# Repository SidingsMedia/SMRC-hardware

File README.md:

<!-- 
SPDX-FileCopyrightText: Copyright (c) 2021 Matthew Nickson 

SPDX-License-Identifier: MIT
-->
# Hardware

This repository contains all of the schematics and PCB files for Sidings
Media Railway Controller. 

## Main Control Board

This is the main component of the SMRC system. It provides a bridge
between the control nodes and the user as well as handling all of the
railway control logic.

## Speed Control Board

This is one of the nodes that helps to control the railway. It provides
power and controls the speed of a train on the tracks

## Relay Board

This node controls isolation sections in your track allowing for
multiple trains to be on the same line without having to use DCC. It has
8 channels allowing for up to 8 seperate isolation sections to be
controlled from one speed controller.

# Licence
This repo uses the [REUSE](https://reuse.software) standard in order to communicate the correct licence for the file. For those unfamiliar with the standard the licence for each file can be found in one of three places. The licence will either be in a comment block at the top of the file, in a `.license` file with the same name as the file, or in the dep5 file located in the `.reuse` directory. If you are unsure of the licencing terms please contact [contact@sidingsmedia.com](mailto:contact@sidingsmedia.com?subject=SMRC%20Licence). All files committed to this repo must contain valid licencing information or the pull request can not be accepted.

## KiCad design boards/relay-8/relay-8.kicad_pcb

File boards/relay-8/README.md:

# 8 Channel relay

This board controls the flow of electricity to the rails when the
railway is in operation allowing for isolation sections to be created.

## Bill of materials

Total number of components: 75

|Ref                                          |Qnty|Value               |Cmp name            |Footprint                                             |Description                                                                                                |Vendor|
|---------------------------------------------|----|--------------------|--------------------|------------------------------------------------------|-----------------------------------------------------------------------------------------------------------|------|
|C1, C3, C5,                                  |3   |1uF                 |C                   |Capacitor_SMD:CP_Elec_4x3                             |Unpolarized capacitor                                                                                      |      |
|C2,                                          |1   |0.1uF               |CP                  |Capacitor_SMD:CP_Elec_4x3                             |                                                                                                           |      |
|C4,                                          |1   |100nF               |C                   |Capacitor_SMD:C_0805_2012Metric                       |Unpolarized capacitor                                                                                      |      |
|D1, D2, D5, D6, D9, D10, D13, D14, D17, D18, |10  |LED                 |LED                 |LED_SMD:LED_0805_2012Metric                           |Light emitting diode                                                                                       |      |
|D3, D4, D7, D8, D11, D12, D15, D16,          |8   |1N5819              |1N5819              |Diode_SMD:D_SMA                                       |40V 1A Schottky Barrier Rectifier Diode, DO-41                                                             |      |
|J1, J3, J4, J5, J6, J7, J8, J9, J10, J11,    |10  |Screw_Terminal_01x02|Screw_Terminal_01x02|TerminalBlock:TerminalBlock_bornier-2_P5.08mm         |Generic screw terminal, single row, 01x02, script generated (kicad-library-utils/schlib/autogen/connector/)|      |
|J2,                                          |1   |USB_B_Micro         |USB_B_Micro         |Connector_USB:USB_Micro-B_Molex_47346-0001            |USB Micro Type B connector                                                                                 |      |
|K1, K2, K3, K4, K5, K6, K7, K8,              |8   |RT42xxxx            |RT42xxxx            |Relay_THT:Relay_DPDT_Schrack-RT2-FormC_RM5mm          |Schrack RT2 relay, monostable dual pole dual throw, DC or AC coil                                          |      |
|Q1, Q2, Q3, Q4, Q5, Q6, Q7, Q8,              |8   |BC847               |BC847               |Package_TO_SOT_SMD:SOT-23                             |0.1A Ic, 45V Vce, NPN Transistor, SOT-23                                                                   |      |
|R1,                                          |1   |10K                 |R                   |Resistor_SMD:R_0805_2012Metric                        |Resistor                                                                                                   |      |
|R2,                                          |1   |560R                |R                   |Resistor_SMD:R_0805_2012Metric                        |Resistor                                                                                                   |      |
|R3, R4, R5, R8, R9, R12, R13, R16, R17,      |9   |330R                |R                   |Resistor_SMD:R_0805_2012Metric                        |Resistor                                                                                                   |      |
|R6, R7, R10, R11, R14, R15, R18, R19,        |8   |1K                  |R                   |Resistor_SMD:R_0805_2012Metric                        |Resistor                                                                                                   |      |
|R20, R21,                                    |2   |R                   |R                   |Resistor_SMD:R_0805_2012Metric                        |Resistor                                                                                                   |      |
|SW1,                                         |1   |SW_Push             |SW_Push             |Button_Switch_SMD:SW_Push_1P1T_NO_6x6mm_H9.5mm        |Push button switch, generic, two pins                                                                      |      |
|U1,                                          |1   |ESP32-WROOM-32D     |ESP32-WROOM-32D     |RF_Module:ESP32-WROOM-32                              |RF Module, ESP32-D0WD SoC, Wi-Fi 802.11b/g/n, Bluetooth, BLE, 32-bit, 2.7-3.6V, onboard antenna, SMD       |      |
|U2,                                          |1   |MCP2200-I-MQ        |MCP2200-I-MQ        |Package_DFN_QFN:QFN-20-1EP_5x5mm_P0.65mm_EP3.35x3.35mm|USB 2.0 to UART Protocol Converter with GPIO, QFN-20                                                       |      |
|U3,                                          |1   |LM317_SOT-223       |LM317_SOT-223       |Package_TO_SOT_SMD:SOT-223-3_TabPin2                  |1.5A 35V Adjustable Linear Regulator, SOT-223                                                              |      |

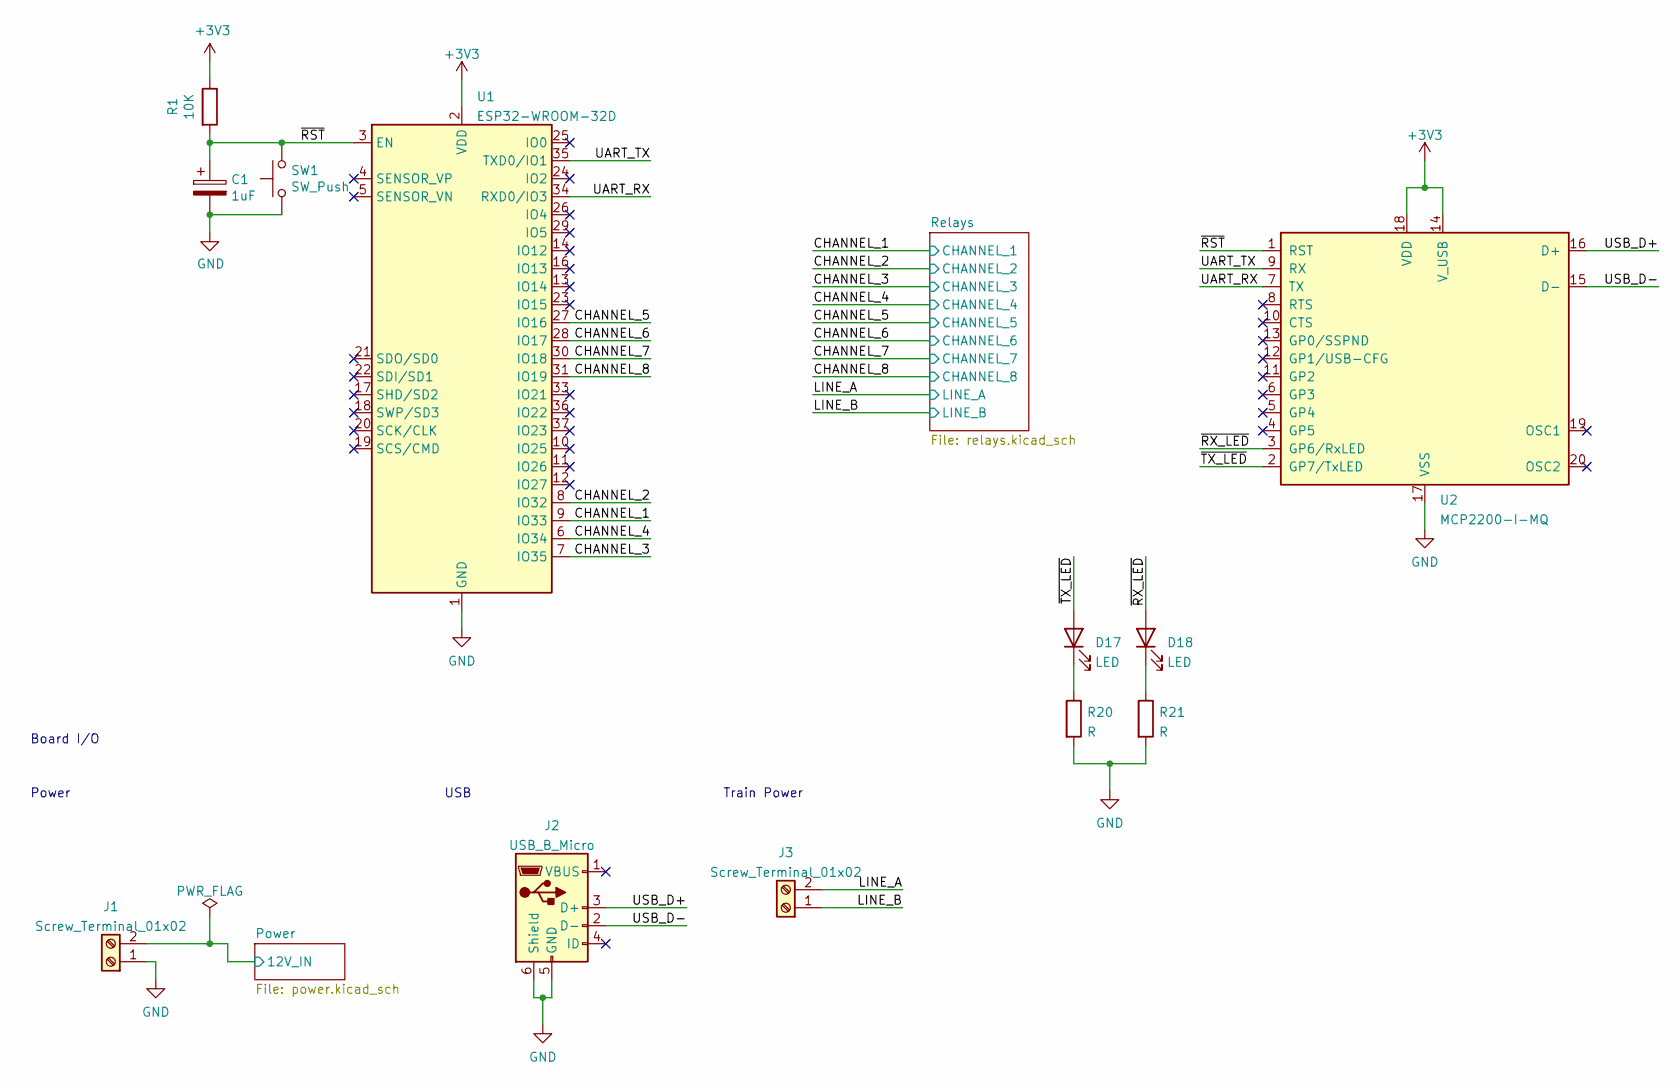
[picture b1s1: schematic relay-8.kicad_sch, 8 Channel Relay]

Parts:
C1: 1uF; CP_Elec_4x3
D17, D18: LED; LED_0805_2012Metric
J1, J3: Screw_Terminal_01x02; TerminalBlock_bornier-2_P5.08mm
J2: USB_B_Micro; USB_Micro-B_Molex_47346-0001
R1: 10K; R_0805_2012Metric
R20, R21: R; R_0805_2012Metric
SW1: SW_Push; SW_Push_1P1T_NO_6x6mm_H9.5mm
U1: ESP32-WROOM-32D; ESP32-WROOM-32
U2: MCP2200-I-MQ; QFN-20-1EP_5x5mm_P0.65mm_EP3.35x3.35mm

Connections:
+3V3: R1.1, U1.2 (VDD), U2.14 (V_USB), U2.18 (VDD); also elsewhere on the board
+12V: J1.2; also elsewhere on the board
/CHANNEL_1: U1.9 (IO33); also elsewhere on the board
/CHANNEL_2: U1.8 (IO32); also elsewhere on the board
/CHANNEL_3: U1.7 (IO35); also elsewhere on the board
/CHANNEL_4: U1.6 (IO34); also elsewhere on the board
/CHANNEL_5: U1.27 (IO16); also elsewhere on the board
/CHANNEL_6: U1.28 (IO17); also elsewhere on the board
/CHANNEL_7: U1.30 (IO18); also elsewhere on the board
/CHANNEL_8: U1.31 (IO19); also elsewhere on the board
/LINE_A: J3.2; also elsewhere on the board
/LINE_B: J3.1; also elsewhere on the board
/UART_RX: U1.34 (RXD0/IO3), U2.7 (TX)
/UART_TX: U1.35 (TXD0/IO1), U2.9 (RX)
/USB_D+: J2.3 (D+), U2.16 (D+)
/USB_D-: J2.2 (D-), U2.15 (D-)
/~RST: C1.1, R1.2, SW1.2, U1.3 (EN), U2.1 (RST)
/~RX_LED: D18.2 (A), U2.3 (GP6/RxLED)
/~TX_LED: D17.2 (A), U2.2 (GP7/TxLED)
GND: C1.2, J1.1, J2.5 (GND), J2.6 (Shield), R20.2, R21.2, SW1.1, U1.1 (GND), U1.15 (GND), U1.38 (GND), U1.39 (GND), U2.17 (VSS); also elsewhere on the board
unnamed: D17.1 (K), R20.1
unnamed: D18.1 (K), R21.1

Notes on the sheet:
Train Power
Board I/O
Power
USB

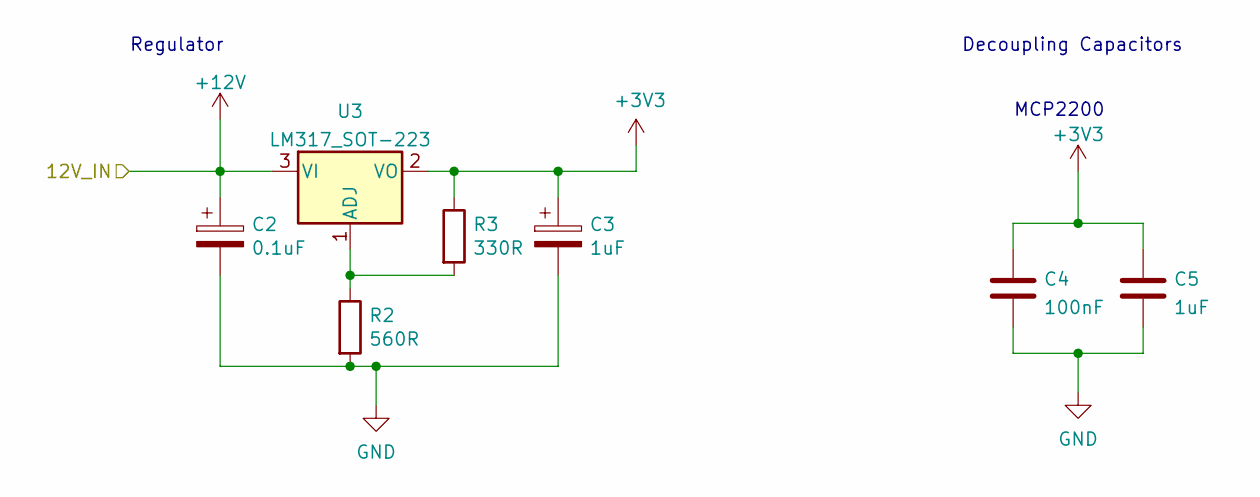
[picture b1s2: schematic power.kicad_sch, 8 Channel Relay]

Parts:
C2: 0.1uF; CP_Elec_4x3
C3, C5: 1uF; CP_Elec_4x3
C4: 100nF; C_0805_2012Metric
R2: 560R; R_0805_2012Metric
R3: 330R; R_0805_2012Metric
U3: LM317_SOT-223; SOT-223-3_TabPin2

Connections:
+3V3: C3.1, C4.1, C5.1, R3.1, U3.2 (VO); also elsewhere on the board
+12V: C2.1, U3.3 (VI); also elsewhere on the board
GND: C2.2, C3.2, C4.2, C5.2, R2.2; also elsewhere on the board
unnamed: R2.1, R3.2, U3.1 (ADJ)

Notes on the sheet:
Regulator
Decoupling Capacitors
MCP2200

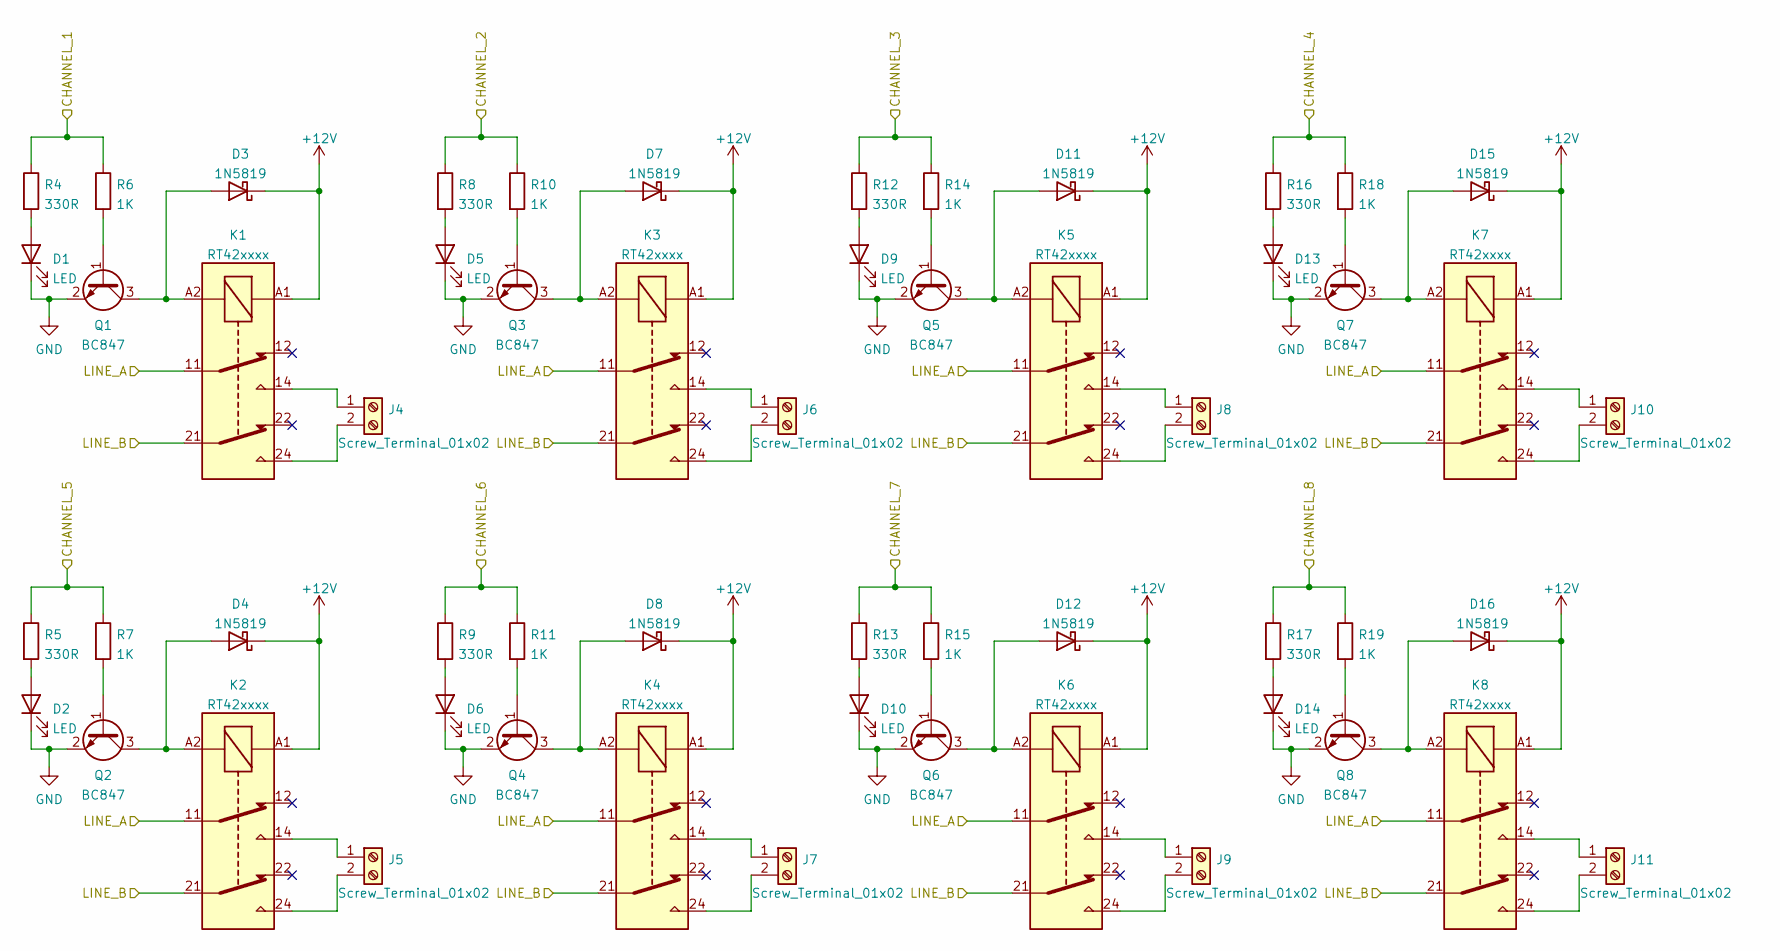
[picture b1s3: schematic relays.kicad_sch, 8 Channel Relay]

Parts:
D1, D2, D5, D6, D9, D10, D13, D14: LED; LED_0805_2012Metric
D3, D4, D7, D8, D11, D12, D15, D16: 1N5819; D_SMA
J4, J5, J6, J7, J8, J9, J10, J11: Screw_Terminal_01x02; TerminalBlock_bornier-2_P5.08mm
K1, K2, K3, K4, K5, K6, K7, K8: RT42xxxx; Relay_DPDT_Schrack-RT2-FormC_RM5mm
Q1, Q2, Q3, Q4, Q5, Q6, Q7, Q8: BC847; SOT-23
R4, R5, R8, R9, R12, R13, R16, R17: 330R; R_0805_2012Metric
R6, R7, R10, R11, R14, R15, R18, R19: 1K; R_0805_2012Metric

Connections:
+12V: D3.1 (K), D4.1 (K), D7.1 (K), D8.1 (K), D11.1 (K), D12.1 (K), D15.1 (K), D16.1 (K), K1.A1, K2.A1, K3.A1, K4.A1, K5.A1, K6.A1, K7.A1, K8.A1; also elsewhere on the board
/CHANNEL_1: R4.1, R6.1; also elsewhere on the board
/CHANNEL_2: R8.1, R10.1; also elsewhere on the board
/CHANNEL_3: R12.1, R14.1; also elsewhere on the board
/CHANNEL_4: R16.1, R18.1; also elsewhere on the board
/CHANNEL_5: R5.1, R7.1; also elsewhere on the board
/CHANNEL_6: R9.1, R11.1; also elsewhere on the board
/CHANNEL_7: R13.1, R15.1; also elsewhere on the board
/CHANNEL_8: R17.1, R19.1; also elsewhere on the board
/LINE_A: K1.11, K2.11, K3.11, K4.11, K5.11, K6.11, K7.11, K8.11; also elsewhere on the board
/LINE_B: K1.21, K2.21, K3.21, K4.21, K5.21, K6.21, K7.21, K8.21; also elsewhere on the board
GND: D1.1 (K), D2.1 (K), D5.1 (K), D6.1 (K), D9.1 (K), D10.1 (K), D13.1 (K), D14.1 (K), Q1.2 (E), Q2.2 (E), Q3.2 (E), Q4.2 (E), Q5.2 (E), Q6.2 (E), Q7.2 (E), Q8.2 (E); also elsewhere on the board
unnamed: D1.2 (A), R4.2
unnamed: D2.2 (A), R5.2
unnamed: D3.2 (A), K1.A2, Q1.3 (C)
unnamed: D4.2 (A), K2.A2, Q2.3 (C)
unnamed: D5.2 (A), R8.2
unnamed: D6.2 (A), R9.2
unnamed: D7.2 (A), K3.A2, Q3.3 (C)
unnamed: D8.2 (A), K4.A2, Q4.3 (C)
unnamed: D9.2 (A), R12.2
unnamed: D10.2 (A), R13.2
unnamed: D11.2 (A), K5.A2, Q5.3 (C)
unnamed: D12.2 (A), K6.A2, Q6.3 (C)
unnamed: D13.2 (A), R16.2
unnamed: D14.2 (A), R17.2
unnamed: D15.2 (A), K7.A2, Q7.3 (C)
unnamed: D16.2 (A), K8.A2, Q8.3 (C)
unnamed: J4.1, K1.14
unnamed: J4.2, K1.24
unnamed: J5.1, K2.14
unnamed: J5.2, K2.24
unnamed: J6.1, K3.14
unnamed: J6.2, K3.24
unnamed: J7.1, K4.14
unnamed: J7.2, K4.24
unnamed: J8.1, K5.14
unnamed: J8.2, K5.24
unnamed: J9.1, K6.14
unnamed: J9.2, K6.24
unnamed: J10.1, K7.14
unnamed: J10.2, K7.24
unnamed: J11.1, K8.14
unnamed: J11.2, K8.24
unnamed: Q1.1 (B), R6.2
unnamed: Q2.1 (B), R7.2
unnamed: Q3.1 (B), R10.2
unnamed: Q4.1 (B), R11.2
unnamed: Q5.1 (B), R14.2
unnamed: Q6.1 (B), R15.2
unnamed: Q7.1 (B), R18.2
unnamed: Q8.1 (B), R19.2

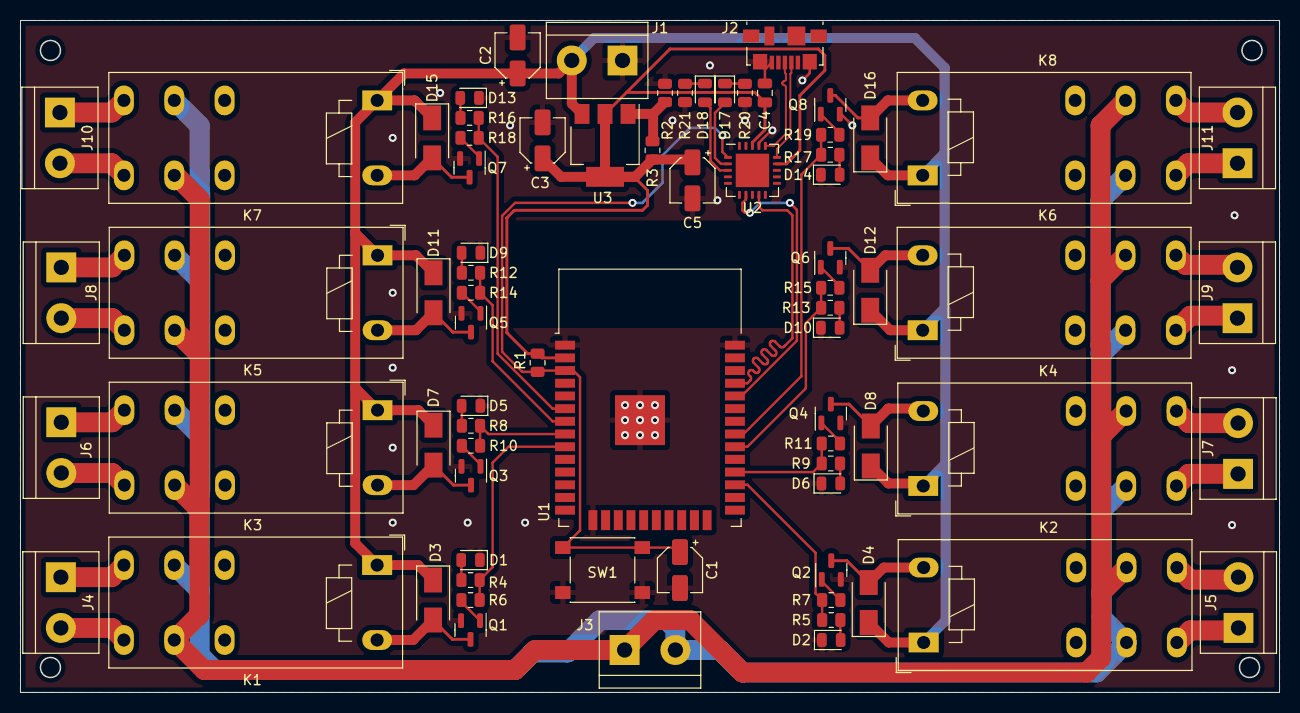
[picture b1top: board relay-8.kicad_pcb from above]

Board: 2 copper layers, 126.0 x 67.2 mm, 75 parts (0 on the bottom side), 63 nets.

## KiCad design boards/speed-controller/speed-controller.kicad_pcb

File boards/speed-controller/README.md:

# Speed controller

This board controls the speed of the trains running on the tracks.

## Bill of materials

Total number of components: 35

|Ref                  |Qnty|Value               |Cmp name            |Footprint                                                               |Description                                                                                                |Vendor|
|---------------------|----|--------------------|--------------------|------------------------------------------------------------------------|-----------------------------------------------------------------------------------------------------------|------|
|C1, C2,              |2   |0.1uF               |CP                  |Capacitor_SMD:CP_Elec_4x3                                               |                                                                                                           |      |
|C3, C4, C6,          |3   |1uF                 |C_Polarized         |Capacitor_SMD:CP_Elec_4x3                                               |Polarized capacitor                                                                                        |      |
|D1, D2, D3, D4,      |4   |1N5820              |1N5820              |Diode_SMD:D_SMC                                                         |20V 3A Schottky Barrier Rectifier Diode, DO-201AD                                                          |      |
|D5, D6,              |2   |LED                 |LED                 |LED_SMD:LED_0805_2012Metric                                             |Light emitting diode                                                                                       |      |
|J1, J2, J3,          |3   |Screw_Terminal_01x02|Screw_Terminal_01x02|TerminalBlock:TerminalBlock_bornier-2_P5.08mm                           |Generic screw terminal, single row, 01x02, script generated (kicad-library-utils/schlib/autogen/connector/)|      |
|J4,                  |1   |USB_B_Micro         |USB_B_Micro         |Connector_USB:USB_Micro-B_Molex_47346-0001                              |USB Micro Type B connector                                                                                 |      |
|Q1, Q2,              |2   |BSS138              |BSS138              |Package_TO_SOT_SMD:SOT-23                                               |50V Vds, 0.22A Id, N-Channel MOSFET, SOT-23                                                                |      |
|R1,                  |1   |1R                  |R                   |Resistor_THT:R_Axial_Power_L20.0mm_W6.4mm_P22.40mm                      |Resistor                                                                                                   |      |
|R2,                  |1   |1K                  |R                   |Resistor_SMD:R_0805_2012Metric                                          |Resistor                                                                                                   |      |
|R3,                  |1   |560R                |R                   |Resistor_SMD:R_0805_2012Metric                                          |Resistor                                                                                                   |      |
|R4, R5,              |2   |330R                |R                   |Resistor_SMD:R_0805_2012Metric                                          |Resistor                                                                                                   |      |
|R6, R7, R8, R9, R10, |5   |10K                 |R                   |Resistor_SMD:R_0805_2012Metric                                          |Resistor                                                                                                   |      |
|R11, R12,            |2   |R                   |R                   |Resistor_SMD:R_0805_2012Metric                                          |Resistor                                                                                                   |      |
|SW1,                 |1   |SW_Push             |SW_Push             |Button_Switch_SMD:SW_Push_1P1T_NO_6x6mm_H9.5mm                          |Push button switch, generic, two pins                                                                      |      |
|U1, U2,              |2   |LM317_SOT-223       |LM317_SOT-223       |Package_TO_SOT_SMD:SOT-223-3_TabPin2                                    |1.5A 35V Adjustable Linear Regulator, SOT-223                                                              |      |
|U3,                  |1   |L298HN              |L298HN              |Package_TO_SOT_THT:TO-220-15_P2.54x2.54mm_StaggerOdd_Lead4.58mm_Vertical|Dual full bridge motor driver, up to 46V, 4A, Multiwatt-15                                                 |      |
|U4,                  |1   |ESP32-WROOM-32D     |ESP32-WROOM-32D     |RF_Module:ESP32-WROOM-32                                                |RF Module, ESP32-D0WD SoC, Wi-Fi 802.11b/g/n, Bluetooth, BLE, 32-bit, 2.7-3.6V, onboard antenna, SMD       |      |
|U5,                  |1   |MCP2200-I-MQ        |MCP2200-I-MQ        |Package_DFN_QFN:QFN-20-1EP_5x5mm_P0.65mm_EP3.35x3.35mm                  |USB 2.0 to UART Protocol Converter with GPIO, QFN-20                                                       |      |

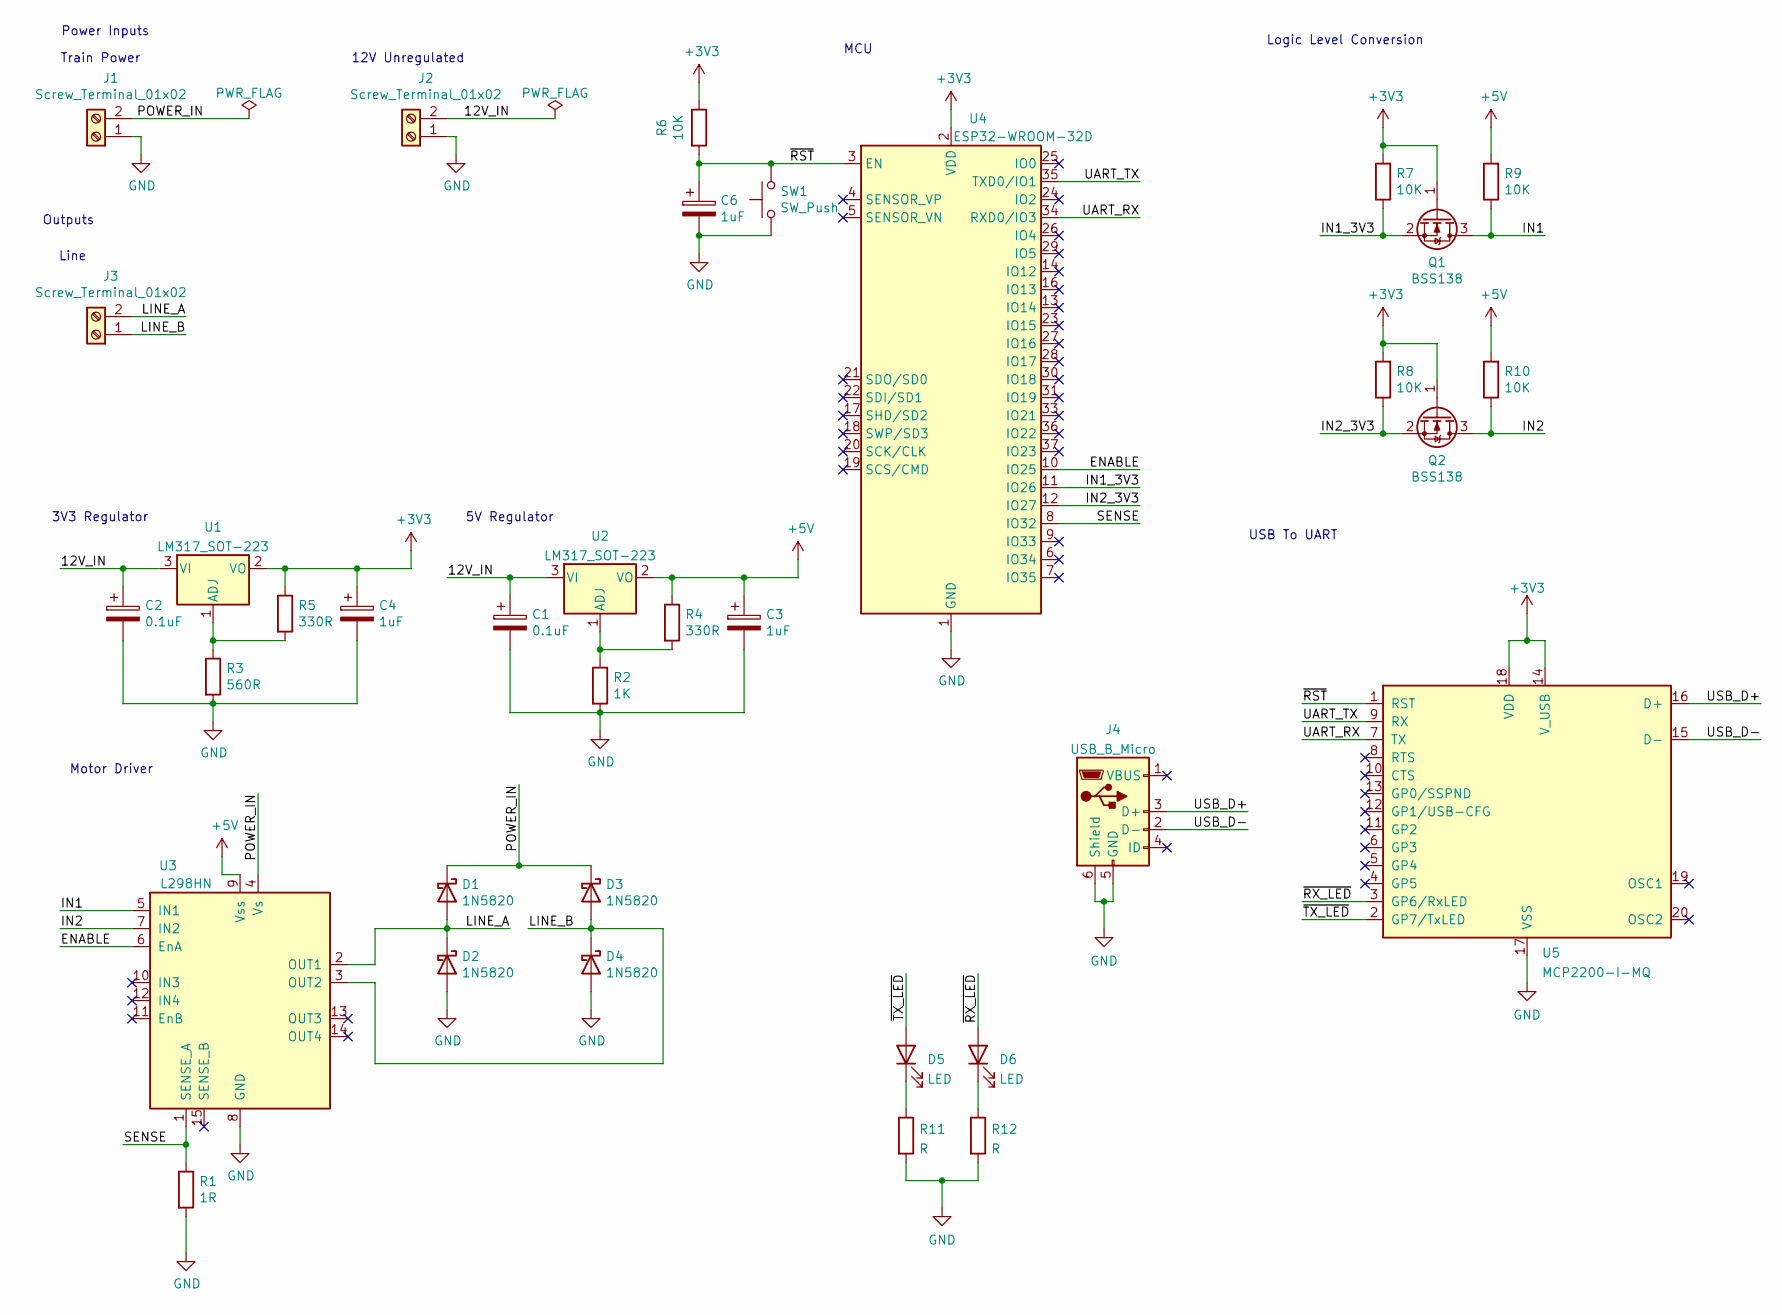
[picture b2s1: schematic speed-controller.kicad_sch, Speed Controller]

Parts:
C1, C2: 0.1uF; CP_Elec_4x3
C3, C4, C6: 1uF; CP_Elec_4x3
D1, D2, D3, D4: 1N5820; D_SMC
D5, D6: LED; LED_0805_2012Metric
J1, J2, J3: Screw_Terminal_01x02; TerminalBlock_bornier-2_P5.08mm
J4: USB_B_Micro; USB_Micro-B_Molex_47346-0001
Q1, Q2: BSS138; SOT-23
R1: 1R; R_Axial_Power_L20.0mm_W6.4mm_P22.40mm
R2: 1K; R_0805_2012Metric
R3: 560R; R_0805_2012Metric
R4, R5: 330R; R_0805_2012Metric
R6, R7, R8, R9, R10: 10K; R_0805_2012Metric
R11, R12: R; R_0805_2012Metric
SW1: SW_Push; SW_Push_1P1T_NO_6x6mm_H9.5mm
U1, U2: LM317_SOT-223; SOT-223-3_TabPin2
U3: L298HN; TO-220-15_P2.54x2.54mm_StaggerOdd_Lead4.58mm_Vertical
U4: ESP32-WROOM-32D; ESP32-WROOM-32
U5: MCP2200-I-MQ; QFN-20-1EP_5x5mm_P0.65mm_EP3.35x3.35mm

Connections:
+3V3: C4.1, Q1.1 (G), Q2.1 (G), R5.1, R6.1, R7.2, R8.2, U1.2 (VO), U4.2 (VDD), U5.14 (V_USB), U5.18 (VDD)
+5V: C3.1, R4.1, R9.2, R10.2, U2.2 (VO), U3.9 (Vss)
/12V_IN: C1.1, C2.1, J2.2, U1.3 (VI), U2.3 (VI)
/ENABLE: U3.6 (EnA), U4.10 (IO25)
/IN1: Q1.3 (D), R9.1, U3.5 (IN1)
/IN1_3V3: Q1.2 (S), R7.1, U4.11 (IO26)
/IN2: Q2.3 (D), R10.1, U3.7 (IN2)
/IN2_3V3: Q2.2 (S), R8.1, U4.12 (IO27)
/LINE_A: D1.2 (A), D2.1 (K), J3.2, U3.2 (OUT1)
/LINE_B: D3.2 (A), D4.1 (K), J3.1, U3.3 (OUT2)
/POWER_IN: D1.1 (K), D3.1 (K), J1.2, U3.4 (Vs)
/SENSE: R1.1, U3.1 (SENSE_A), U4.8 (IO32)
/UART_RX: U4.34 (RXD0/IO3), U5.7 (TX)
/UART_TX: U4.35 (TXD0/IO1), U5.9 (RX)
/USB_D+: J4.3 (D+), U5.16 (D+)
/USB_D-: J4.2 (D-), U5.15 (D-)
/~RST: C6.1, R6.2, SW1.2, U4.3 (EN), U5.1 (RST)
/~RX_LED: D6.2 (A), U5.3 (GP6/RxLED)
/~TX_LED: D5.2 (A), U5.2 (GP7/TxLED)
GND: C1.2, C2.2, C3.2, C4.2, C6.2, D2.2 (A), D4.2 (A), J1.1, J2.1, J4.5 (GND), J4.6 (Shield), R1.2, R2.2, R3.2, R11.2, R12.2, SW1.1, U3.8 (GND), U4.1 (GND), U4.15 (GND), U4.38 (GND), U4.39 (GND), U5.17 (VSS)
unnamed: D5.1 (K), R11.1
unnamed: D6.1 (K), R12.1
unnamed: R2.1, R4.2, U2.1 (ADJ)
unnamed: R3.1, R5.2, U1.1 (ADJ)

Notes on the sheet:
Train Power
MCU
12V Unregulated
Logic Level Conversion
5V Regulator
Motor Driver
USB To UART
3V3 Regulator
Power Inputs
Outputs
Line

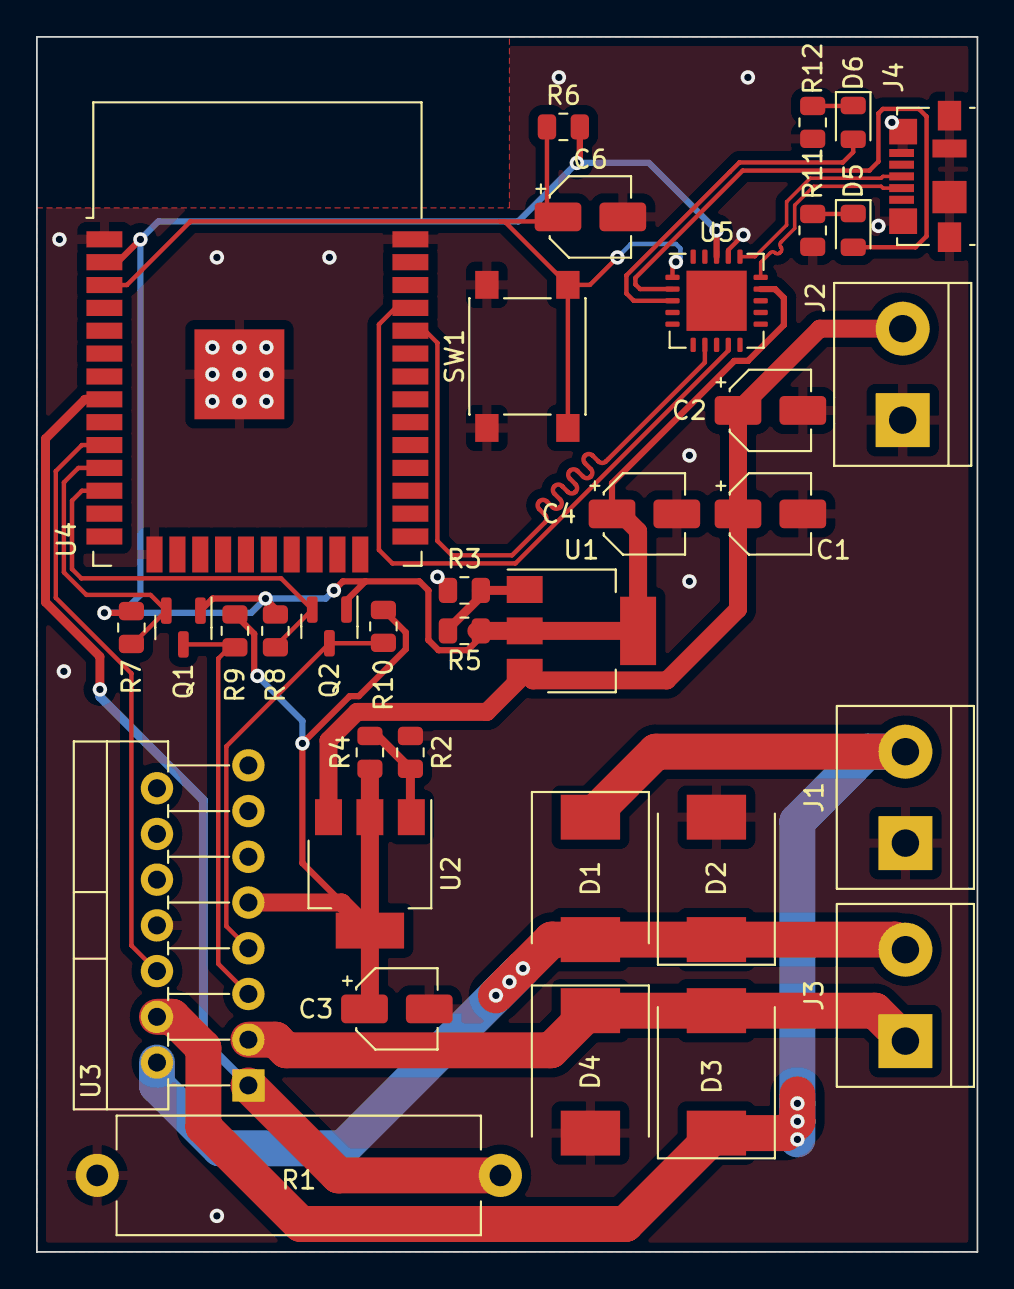
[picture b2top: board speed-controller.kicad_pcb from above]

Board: 2 copper layers, 52.2 x 67.5 mm, 35 parts (0 on the bottom side), 24 nets.

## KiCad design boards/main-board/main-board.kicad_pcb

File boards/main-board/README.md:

# Main Board

This board forms the bridge between all of the interface nodes and the
client software. All commands pass through this board and it is
responsible for all of the railway control logic.

## Bill of materials

Total number of components: 68

|Ref                                             |Qnty|Value               |Cmp name            |Footprint                                                 |Description                                                                                                |Vendor|
|------------------------------------------------|----|--------------------|--------------------|----------------------------------------------------------|-----------------------------------------------------------------------------------------------------------|------|
|C1, C2,                                         |2   |27pF                |C                   |Capacitor_SMD:C_0805_2012Metric                           |Unpolarized capacitor                                                                                      |      |
|C3, C4, C5, C6, C7, C8, C9, C10, C13, C14, C17, |11  |100nF               |C                   |Capacitor_SMD:C_0805_2012Metric                           |Unpolarized capacitor                                                                                      |      |
|C11,                                            |1   |0.1uF               |C_Polarized         |Capacitor_SMD:CP_Elec_4x3                                 |Polarized capacitor                                                                                        |      |
|C12, C18,                                       |2   |1uF                 |C_Polarized         |Capacitor_SMD:CP_Elec_4x3                                 |Polarized capacitor                                                                                        |      |
|C15, C16,                                       |2   |1uF                 |C                   |Capacitor_SMD:C_0805_2012Metric                           |Unpolarized capacitor                                                                                      |      |
|C19,                                            |1   |45uF                |C                   |Capacitor_SMD:CP_Elec_4x3                                 |Unpolarized capacitor                                                                                      |      |
|C20, C21,                                       |2   |30pF                |C                   |Capacitor_SMD:C_0805_2012Metric                           |Unpolarized capacitor                                                                                      |      |
|C22, C23, C24,                                  |3   |10nF                |C                   |Capacitor_SMD:C_0805_2012Metric                           |Unpolarized capacitor                                                                                      |      |
|FB1,                                            |1   |FerriteBead         |FerriteBead         |Resistor_SMD:R_0805_2012Metric                            |Ferrite bead                                                                                               |      |
|J1,                                             |1   |Screw_Terminal_01x02|Screw_Terminal_01x02|TerminalBlock:TerminalBlock_Altech_AK300-2_P5.00mm        |Generic screw terminal, single row, 01x02, script generated (kicad-library-utils/schlib/autogen/connector/)|      |
|J2,                                             |1   |USB_B_Micro         |USB_B_Micro         |Connector_USB:USB_Micro-B_Molex_47346-0001                |USB Micro Type B connector                                                                                 |      |
|J3,                                             |1   |RJ45_Bel_SI-60062-F |RJ45_Bel_SI-60062-F |Connector_RJ:RJ45_Bel_SI-60062-F                          |1 Port RJ45 Magjack Connector Through Hole 10/100 Base-T, AutoMDIX                                         |      |
|J4,                                             |1   |Micro_SD_Card_Det   |Micro_SD_Card_Det   |Connector_Card:microSD_HC_Molex_104031-0811               |Micro SD Card Socket with card detection pins                                                              |      |
|J5, J6,                                         |2   |DNF                 |Conn_01x04_Male     |Connector_PinHeader_2.54mm:PinHeader_1x04_P2.54mm_Vertical|Generic connector, single row, 01x04, script generated (kicad-library-utils/schlib/autogen/connector/)     |      |
|JP1,                                            |1   |DNF                 |Jumper_2_Open       |Jumper:SolderJumper-2_P1.3mm_Open_Pad1.0x1.5mm            |Jumper, 2-pole, open                                                                                       |      |
|R1, R4, R7, R22,                                |4   |1K                  |R                   |Resistor_SMD:R_0805_2012Metric                            |Resistor                                                                                                   |      |
|R2, R27, R28,                                   |3   |330R                |R                   |Resistor_SMD:R_0805_2012Metric                            |Resistor                                                                                                   |      |
|R3,                                             |1   |560R                |R                   |Resistor_SMD:R_0805_2012Metric                            |Resistor                                                                                                   |      |
|R5, R6,                                         |2   |27R                 |R                   |Resistor_SMD:R_0805_2012Metric                            |Resistor                                                                                                   |      |
|R8,                                             |1   |10K                 |R                   |Resistor_SMD:R_0805_2012Metric                            |Resistor                                                                                                   |      |
|R9, R10, R11, R12,                              |4   |10R                 |R                   |Resistor_SMD:R_0805_2012Metric                            |Resistor                                                                                                   |      |
|R13,                                            |1   |1K5                 |R                   |Resistor_SMD:R_0805_2012Metric                            |Resistor                                                                                                   |      |
|R14,                                            |1   |12K1                |R                   |Resistor_SMD:R_0805_2012Metric                            |Resistor                                                                                                   |      |
|R15, R16, R17, R18, R19, R20, R21,              |7   |47K                 |R                   |Resistor_SMD:R_0805_2012Metric                            |Resistor                                                                                                   |      |
|R23, R24, R25, R26,                             |4   |49.9R               |R                   |Resistor_SMD:R_0805_2012Metric                            |Resistor                                                                                                   |      |
|SW1,                                            |1   |SW_Push             |SW_Push             |Button_Switch_SMD:SW_Push_1P1T_NO_6x6mm_H9.5mm            |Push button switch, generic, two pins                                                                      |      |
|U1,                                             |1   |W25Q128JVS          |W25Q128JVS          |Package_SO:SOIC-8_5.23x5.23mm_P1.27mm                     |128Mb Serial Flash Memory, Standard/Dual/Quad SPI, SOIC-8                                                  |      |
|U2,                                             |1   |RP2040              |RP2040              |RP2040_minimal:RP2040-QFN-56                              |                                                                                                           |      |
|U3,                                             |1   |LM317               |LM317_SOT-223       |Package_TO_SOT_SMD:SOT-223-3_TabPin2                      |1.5A 35V Adjustable Linear Regulator, SOT-223                                                              |      |
|U4,                                             |1   |ESP32-WROOM-32D     |ESP32-WROOM-32D     |RF_Module:ESP32-WROOM-32                                  |RF Module, ESP32-D0WD SoC, Wi-Fi 802.11b/g/n, Bluetooth, BLE, 32-bit, 2.7-3.6V, onboard antenna, SMD       |      |
|U5,                                             |1   |LAN8720A            |LAN8720A            |Package_DFN_QFN:QFN-24-1EP_4x4mm_P0.5mm_EP2.6x2.6mm       |LAN8720 Ethernet PHY with RMII interface, QFN-24                                                           |      |
|Y1,                                             |1   |ABLS-12.000MHz-B4-T |Crystal             |Crystal:Crystal_SMD_HC49-SD                               |Two pin crystal                                                                                            |      |
|Y2,                                             |1   |25MHz               |Crystal             |Crystal:Crystal_SMD_HC49-SD                               |Two pin crystal                                                                                            |      |

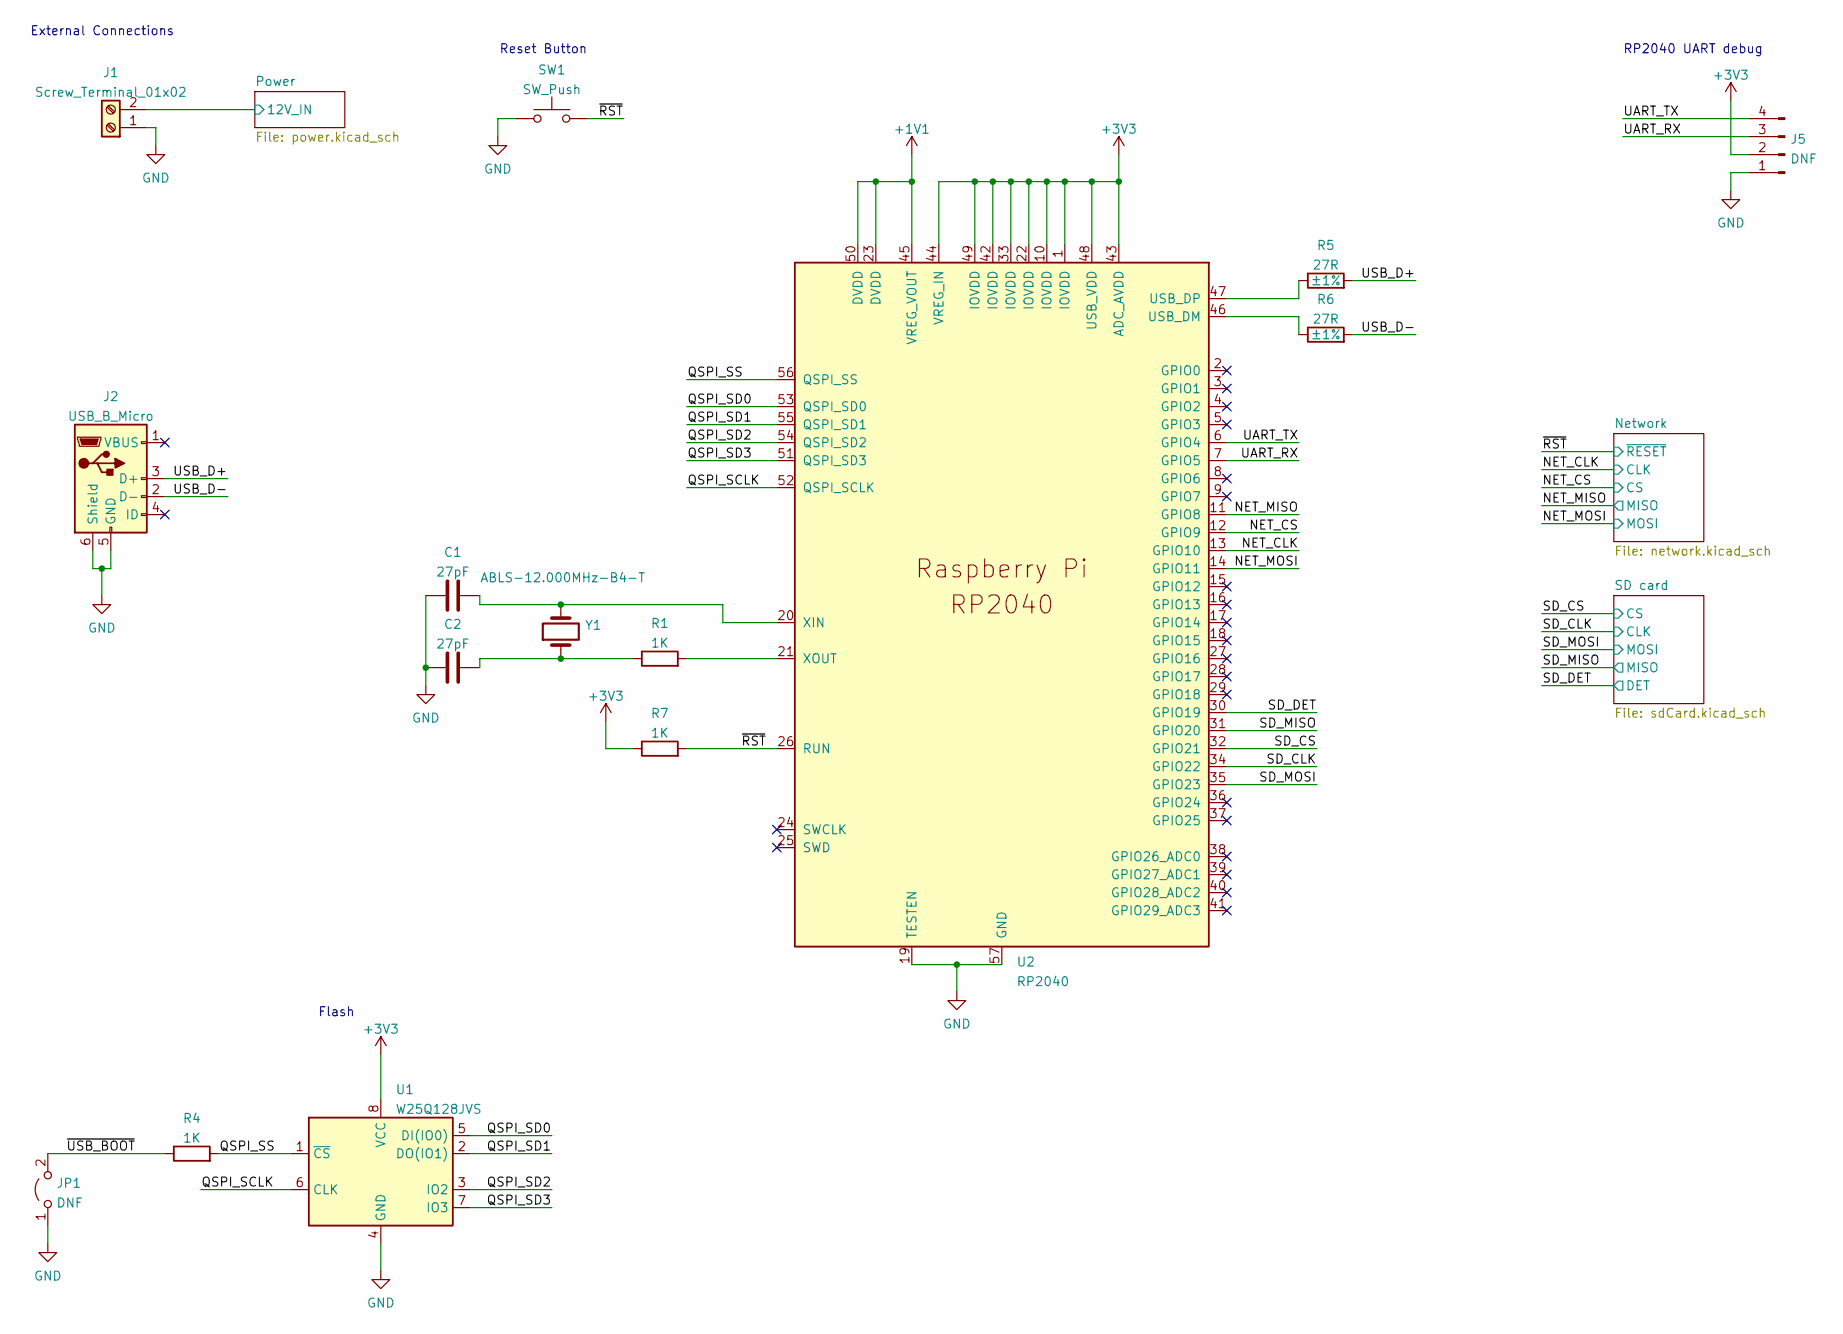
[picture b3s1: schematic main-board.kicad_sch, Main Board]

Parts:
C1, C2: 27pF; C_0805_2012Metric
J1: Screw_Terminal_01x02; TerminalBlock_Altech_AK300-2_P5.00mm
J2: USB_B_Micro; USB_Micro-B_Molex_47346-0001
J5: DNF; PinHeader_1x04_P2.54mm_Vertical
JP1: DNF; SolderJumper-2_P1.3mm_Open_Pad1.0x1.5mm
R1, R4, R7: 1K; R_0805_2012Metric
R5, R6: 27R; R_0805_2012Metric; Tolerance ±1%
SW1: SW_Push; SW_Push_1P1T_NO_6x6mm_H9.5mm
U1: W25Q128JVS; SOIC-8_5.23x5.23mm_P1.27mm
U2: RP2040; RP2040-QFN-56
Y1: ABLS-12.000MHz-B4-T; Crystal_SMD_HC49-SD

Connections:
+1V1: U2.23 (DVDD), U2.45 (VREG_VOUT), U2.50 (DVDD); also elsewhere on the board
+3V3: J5.2, R7.1, U1.8 (VCC), U2.1 (IOVDD), U2.10 (IOVDD), U2.22 (IOVDD), U2.33 (IOVDD), U2.42 (IOVDD), U2.43 (ADC_AVDD), U2.44 (VREG_IN), U2.48 (USB_VDD), U2.49 (IOVDD); also elsewhere on the board
/NET_CLK: U2.13 (GPIO10); also elsewhere on the board
/NET_CS: U2.12 (GPIO9); also elsewhere on the board
/NET_MISO: U2.11 (GPIO8); also elsewhere on the board
/NET_MOSI: U2.14 (GPIO11); also elsewhere on the board
/Power/12V_IN: J1.2; also elsewhere on the board
/QSPI_SCLK: U1.6 (CLK), U2.52 (QSPI_SCLK)
/QSPI_SD0: U1.5 (DI(IO0)), U2.53 (QSPI_SD0)
/QSPI_SD1: U1.2 (DO(IO1)), U2.55 (QSPI_SD1)
/QSPI_SD2: U1.3 (IO2), U2.54 (QSPI_SD2)
/QSPI_SD3: U1.7 (IO3), U2.51 (QSPI_SD3)
/QSPI_SS: R4.2, U1.1 (~CS), U2.56 (QSPI_SS)
/SD_CLK: U2.34 (GPIO22); also elsewhere on the board
/SD_CS: U2.32 (GPIO21); also elsewhere on the board
/SD_DET: U2.30 (GPIO19); also elsewhere on the board
/SD_MISO: U2.31 (GPIO20); also elsewhere on the board
/SD_MOSI: U2.35 (GPIO23); also elsewhere on the board
/UART_RX: J5.3, U2.7 (GPIO5)
/UART_TX: J5.4, U2.6 (GPIO4)
/USB_D+: J2.3 (D+), R5.2
/USB_D-: J2.2 (D-), R6.2
/~RST: R7.2, SW1.2, U2.26 (RUN); also elsewhere on the board
/~USB_BOOT: JP1.2 (B), R4.1
GND: C1.1, C2.1, J1.1, J2.5 (GND), J2.6 (Shield), J5.1, JP1.1 (A), SW1.1, U1.4 (GND), U2.19 (TESTEN), U2.57 (GND); also elsewhere on the board
unnamed: C1.2, U2.20 (XIN), Y1.2
unnamed: C2.2, R1.1, Y1.1
unnamed: R1.2, U2.21 (XOUT)
unnamed: R5.1, U2.47 (USB_DP)
unnamed: R6.1, U2.46 (USB_DM)

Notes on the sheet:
External Connections
Reset Button
RP2040 UART debug
Flash

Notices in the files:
boards/main-board/main-board.kicad_pcb:
Licence: CC-BY-SA-4.0
CC-BY-SA-4.0
